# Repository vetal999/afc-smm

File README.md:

afc-smm
=======

project for my master degree diploma

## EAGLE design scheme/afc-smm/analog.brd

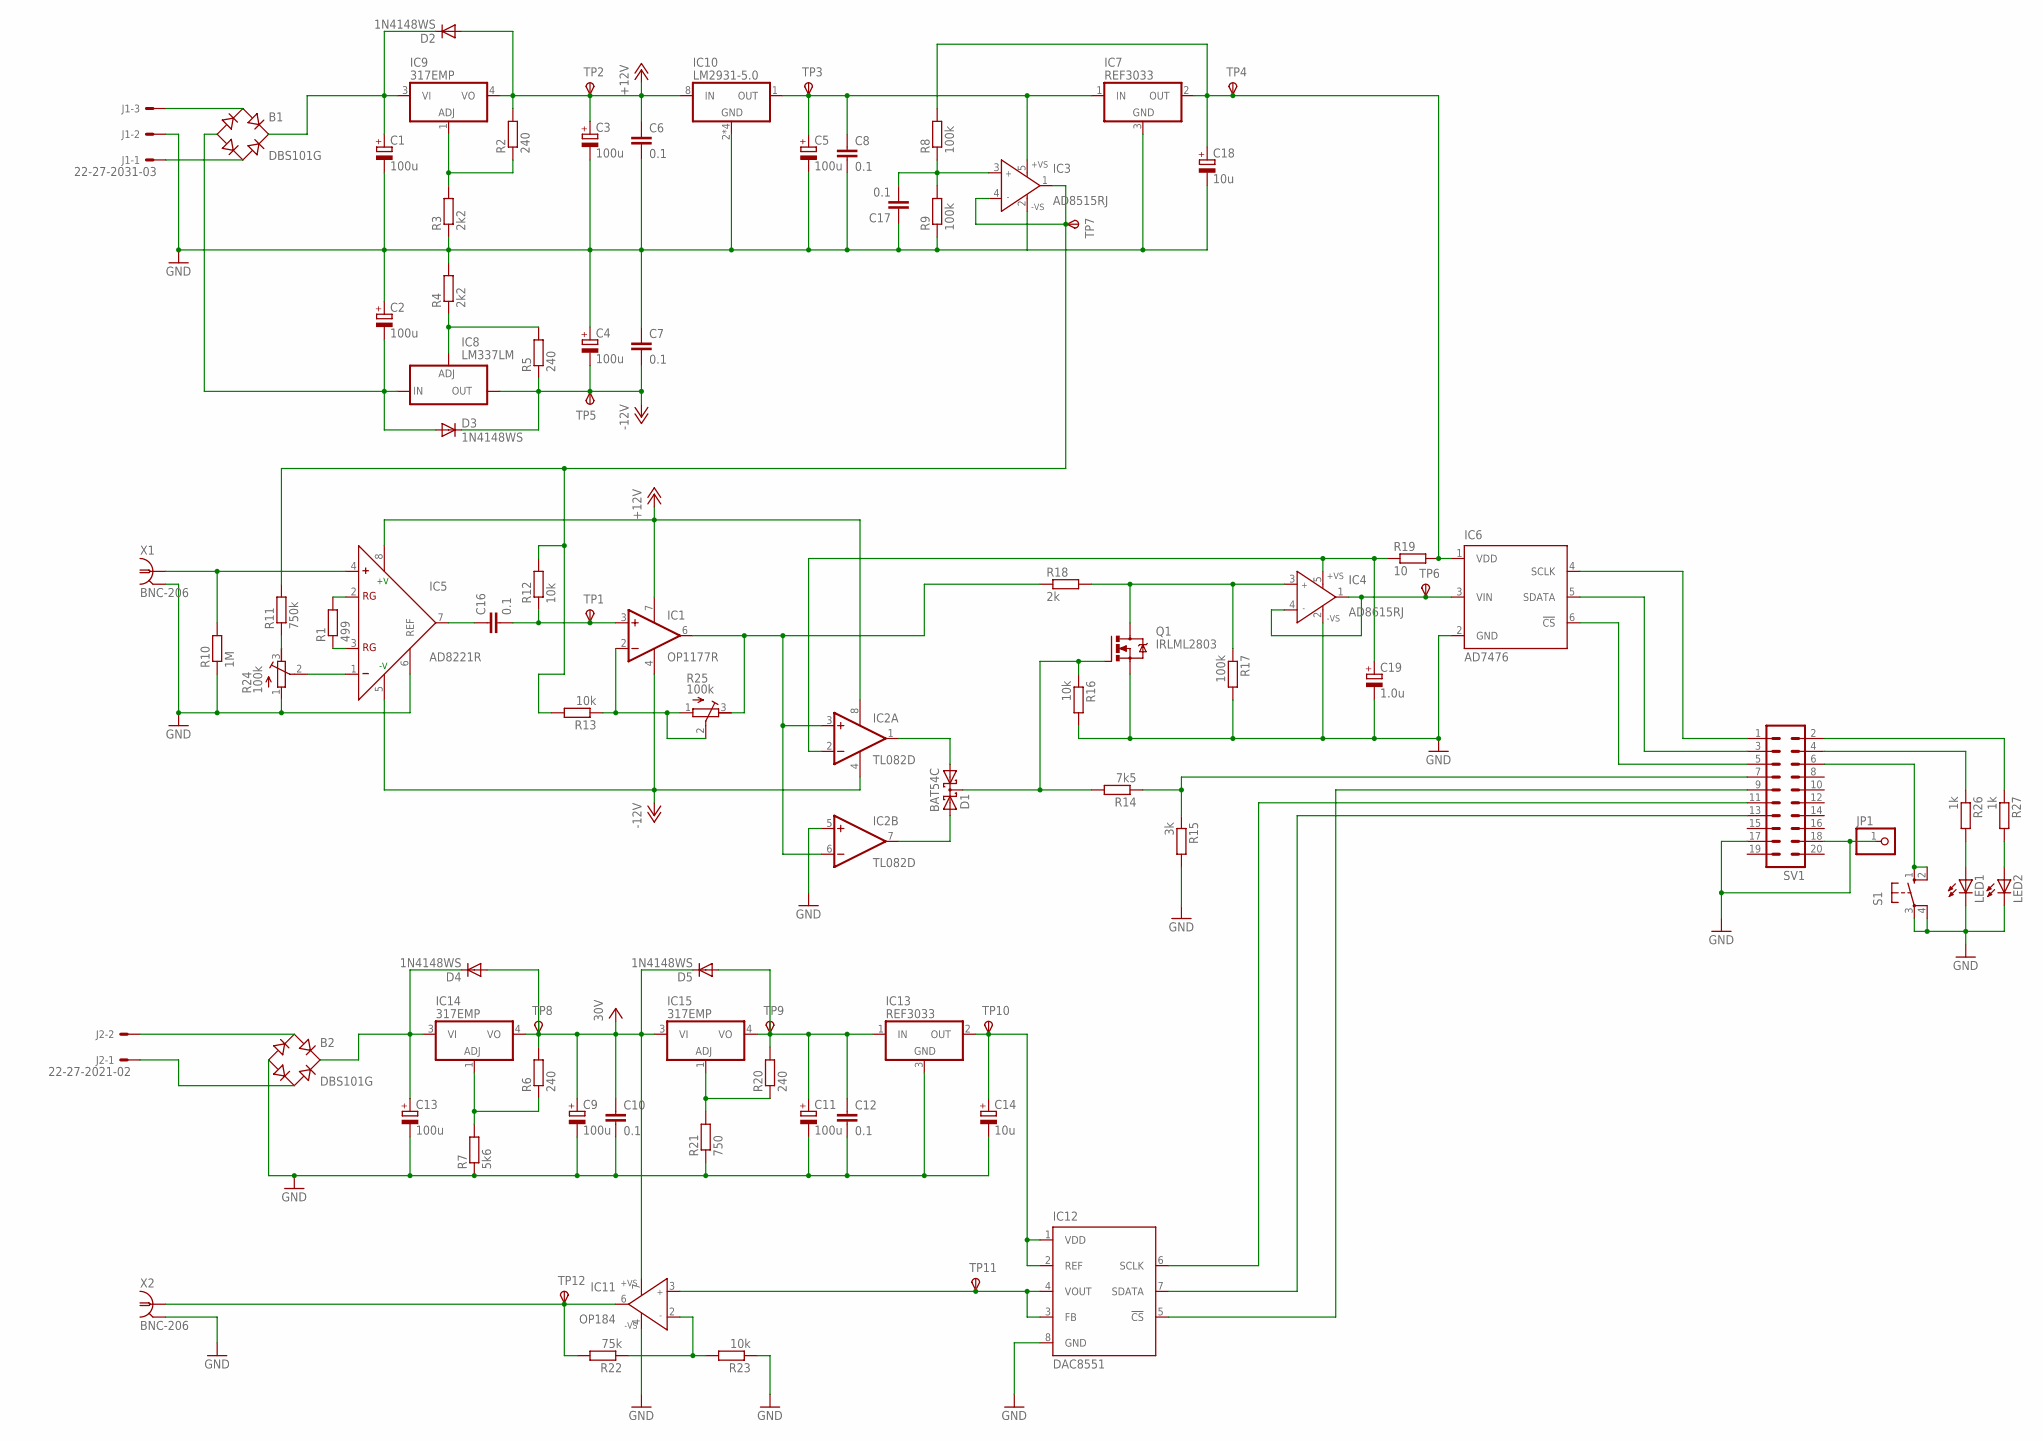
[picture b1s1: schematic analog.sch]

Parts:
B1, B2: DBS101G; DBS
C1, C2, C13: 100u; E3,5-8
C3, C4, C9: 100u; E2,5-6
C5, C11: 100u; E2,5-5
C6, C7, C10: 0.1; C0805K
C8, C12, C16, C17: 0.1; C0603
C14, C18: 10u; SMC_A
C19: 1.0u; SMC_A
D1: BAT54C; SOT23
D2, D3, D4, D5: 1N4148WS; SOD323
IC1: OP1177R; SOIC8
IC2: TL082D; SO08
IC3: AD8515RJ; SOT23-5
IC4: AD8615RJ; SOT23-5
IC5: AD8221R; SO8@1
IC6: AD7476; SOT23-6
IC7, IC13: REF3033; SOT23
IC8: LM337LM; SO8
IC9, IC14, IC15: 317EMP; SOT223
IC10: LM2931-5.0; SO8
IC11: OP184; SO8
IC12: DAC8551; MSOP8
J1: 22-27-2031-03; 6410-03
J2: 22-27-2021-02; 6410-02
JP1: PINHD-1X1; 1X01
LED1, LED2: LEDCHIPLED_0805; CHIPLED_0805
Q1: IRLML2803; SOT23
R1: 499; R0805
R2, R5, R6: 240; R0805
R3, R4: 2k2; R0805
R7: 5k6; R0805
R8, R9, R17: 100k; R0603
R10: 1M; R0603
R11: 750k; R0603
R12, R13, R16, R23: 10k; R0603
R14: 7k5; R0603
R15: 3k; R0603
R18: 2k; R0603
R19: 10; R0603
R20: 240; R0603
R21: 750; R0603
R22: 75k; R0603
R24, R25: 100k; RTRIM3296W
R26, R27: 1k; R0603
S1: 10-XX; B3F-10XX
SV1: MA10-2W
TP1, TP2, TP3, TP4, TP5, TP6, TP7, TP8, TP9, TP10, TP11, TP12: TPSB2,54; B2,54
X1, X2: BNC-206; AMP_227161

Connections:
30V: C9.+, C10.1, D4.2 (A), D5.1 (C), IC11.7 (+VS), IC14.4 (VO), IC15.3 (VI), R6.2, TP8.TP
+3.3V: C18.+, IC6.1 (VDD), IC7.2 (OUT), R8.2, R19.2, TP4.TP
+5V: C5.+, C8.1, IC3.5 (+VS), IC7.1 (IN), IC10.1 (OUT), TP3.TP
+12V: C3.+, C6.1, D2.2 (A), IC1.7 (V+), IC2.8 (V+), IC5.8 (+V), IC9.4 (VO), IC10.8 (IN), R2.2, TP2.TP
-12V: C4.-, C7.2, D3.1 (C), IC1.4 (V-), IC2.4 (V-), IC5.5 (-V), IC8.1 (OUT), R5.1, TP5.TP
GND: B2.-, C1.-, C2.+, C3.-, C4.+, C5.-, C6.2, C7.1, C8.2, C9.-, C10.2, C11.-, C12.2, C13.-, C14.-, C17.1, C18.-, C19.-, IC2.5 (+IN), IC3.2 (-VS), IC4.2 (-VS), IC5.6 (REF), IC6.2 (GND), IC7.3 (GND), IC10.2 (GND), IC10.3 (GND), IC10.6 (GND), IC10.7 (GND), IC11.4 (-VS), IC12.8 (GND), IC13.3 (GND), J1.2, JP1.1, LED1.C, LED2.C, Q1.2 (S), R3.1, R4.2, R7.1, R9.1, R10.1, R15.2, R16.2, R17.2, R21.1, R23.1, R24.1 (A), S1.3, S1.4 (P1), SV1.17, SV1.18, X1.2, X2.2
unnamed: IC4.1 (OUT), IC4.4 (IN-), IC6.3 (VIN), TP6.TP
unnamed: IC4.3 (IN+), Q1.3 (D), R17.1, R18.2
unnamed: B1.-, C2.-, D3.2 (A), IC8.2 (IN), IC8.3 (IN), IC8.6 (IN), IC8.7 (IN)
unnamed: D1.1 (A1), IC2.1 (OUT)
unnamed: D1.3 (CC), Q1.1 (G), R14.2, R16.1
unnamed: D1.2 (A2), IC2.7 (OUT)
unnamed: R26.1, SV1.4
unnamed: R14.1, R15.1, SV1.7
unnamed: IC1.6 (OUT), IC2.3 (+IN), IC2.6 (-IN), R18.1, R25.3 (E)
unnamed: IC5.2 (RG), R1.2
unnamed: IC5.3 (RG), R1.1
unnamed: C16.1, IC5.7 (OUT)
unnamed: IC1.2 (-IN), R13.1, R25.1 (A), R25.2 (S)
unnamed: IC6.4 (SCLK), SV1.1
unnamed: C16.2, IC1.3 (+IN), R12.1, TP1.TP
unnamed: LED1.A, R26.2
unnamed: IC5.1 (-), R24.2 (S)
unnamed: R11.1, R24.3 (E)
unnamed: IC5.4 (+), R10.2, X1.1
unnamed: LED2.A, R27.2
unnamed: IC6.5 (SDATA), SV1.3
unnamed: IC6.6 (!CS), SV1.5
unnamed: B2.AC1, J2.2
unnamed: IC8.4 (ADJ), R4.1, R5.2
unnamed: IC9.1 (ADJ), R2.1, R3.2
unnamed: R27.1, SV1.2
unnamed: C19.+, IC2.2 (-IN), IC4.5 (+VS), R19.1
unnamed: IC3.1 (OUT), IC3.4 (IN-), R11.2, R12.2, R13.2, TP7.TP
unnamed: C17.2, IC3.3 (IN+), R8.1, R9.2
unnamed: B2.+, C13.+, D4.1 (C), IC14.3 (VI)
unnamed: C11.+, C12.1, D5.2 (A), IC13.1 (IN), IC15.4 (VO), R20.2, TP9.TP
unnamed: IC14.1 (ADJ), R6.1, R7.2
unnamed: B1.AC1, J1.3
unnamed: B1.AC2, J1.1
unnamed: IC15.1 (ADJ), R20.1, R21.2
unnamed: B1.+, C1.+, D2.1 (C), IC9.3 (VI)
unnamed: C14.+, IC12.1 (VDD), IC12.2 (REF), IC13.2 (OUT), TP10.TP
unnamed: IC12.6 (SCLK), SV1.11
unnamed: IC11.6 (OUT), R22.2, TP12.TP, X2.1
unnamed: IC12.7 (SDATA), SV1.13
unnamed: IC11.2 (IN-), R22.1, R23.2
unnamed: IC12.5 (!CS), SV1.9
unnamed: IC11.3 (IN+), IC12.3 (FB), IC12.4 (VOUT), TP11.TP
unnamed: B2.AC2, J2.1
unnamed: S1.1 (S), S1.2 (S1), SV1.6

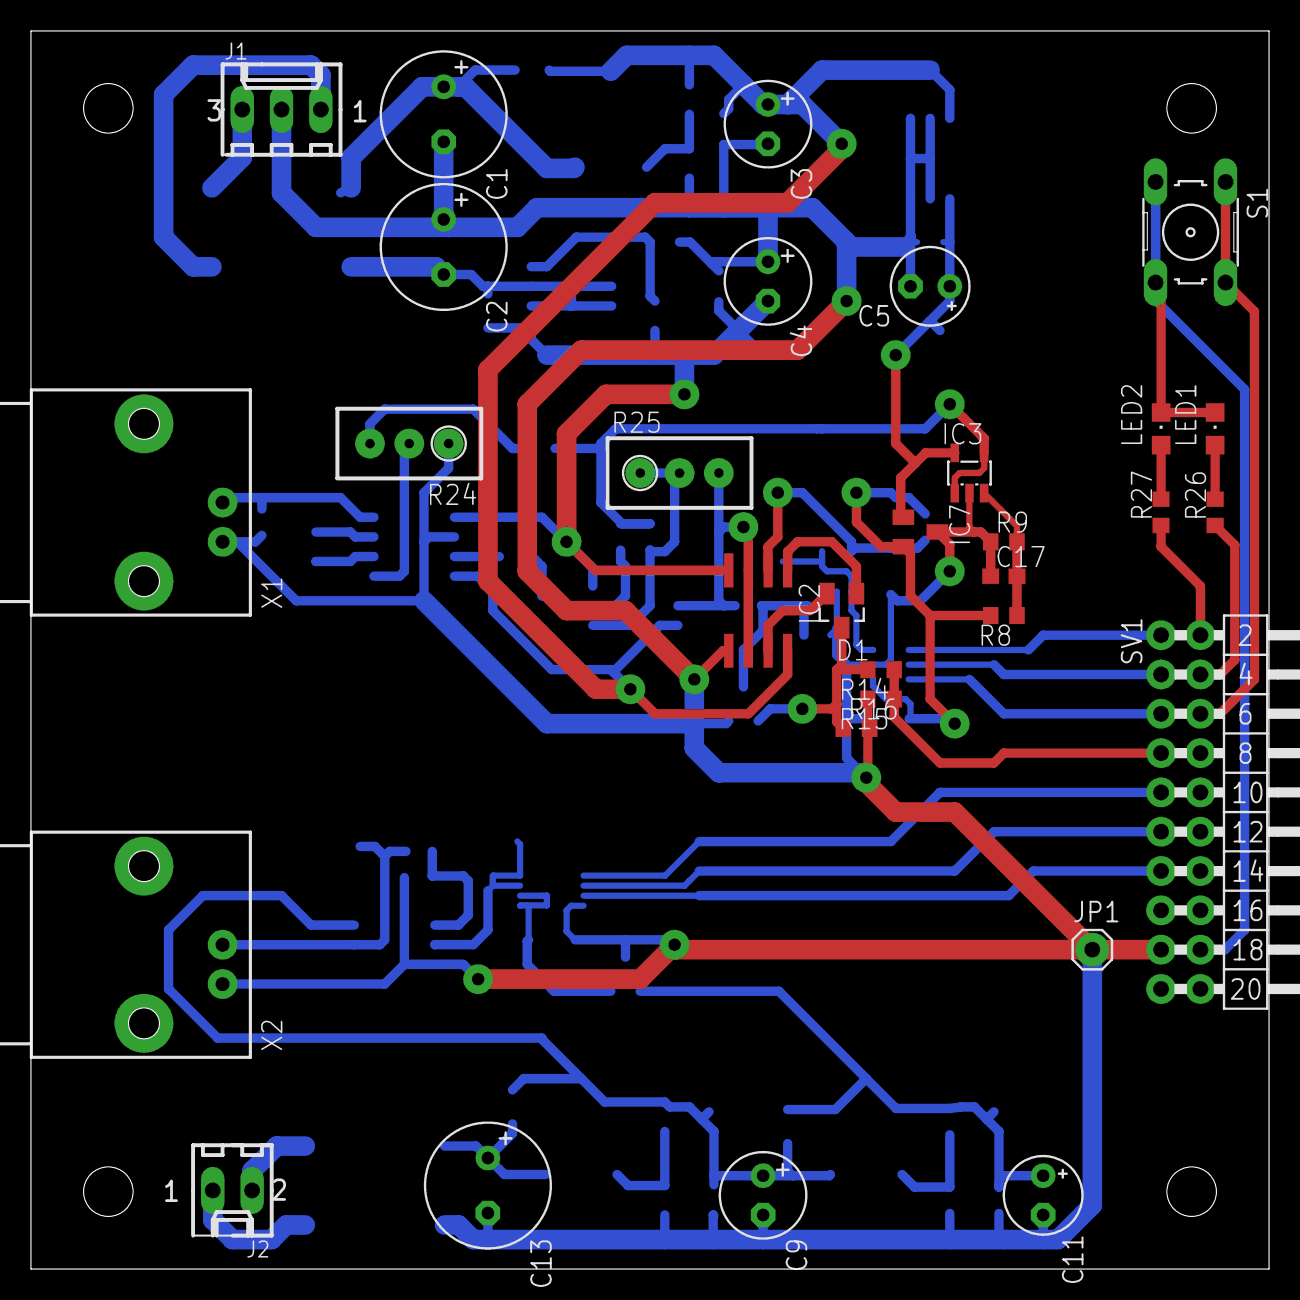
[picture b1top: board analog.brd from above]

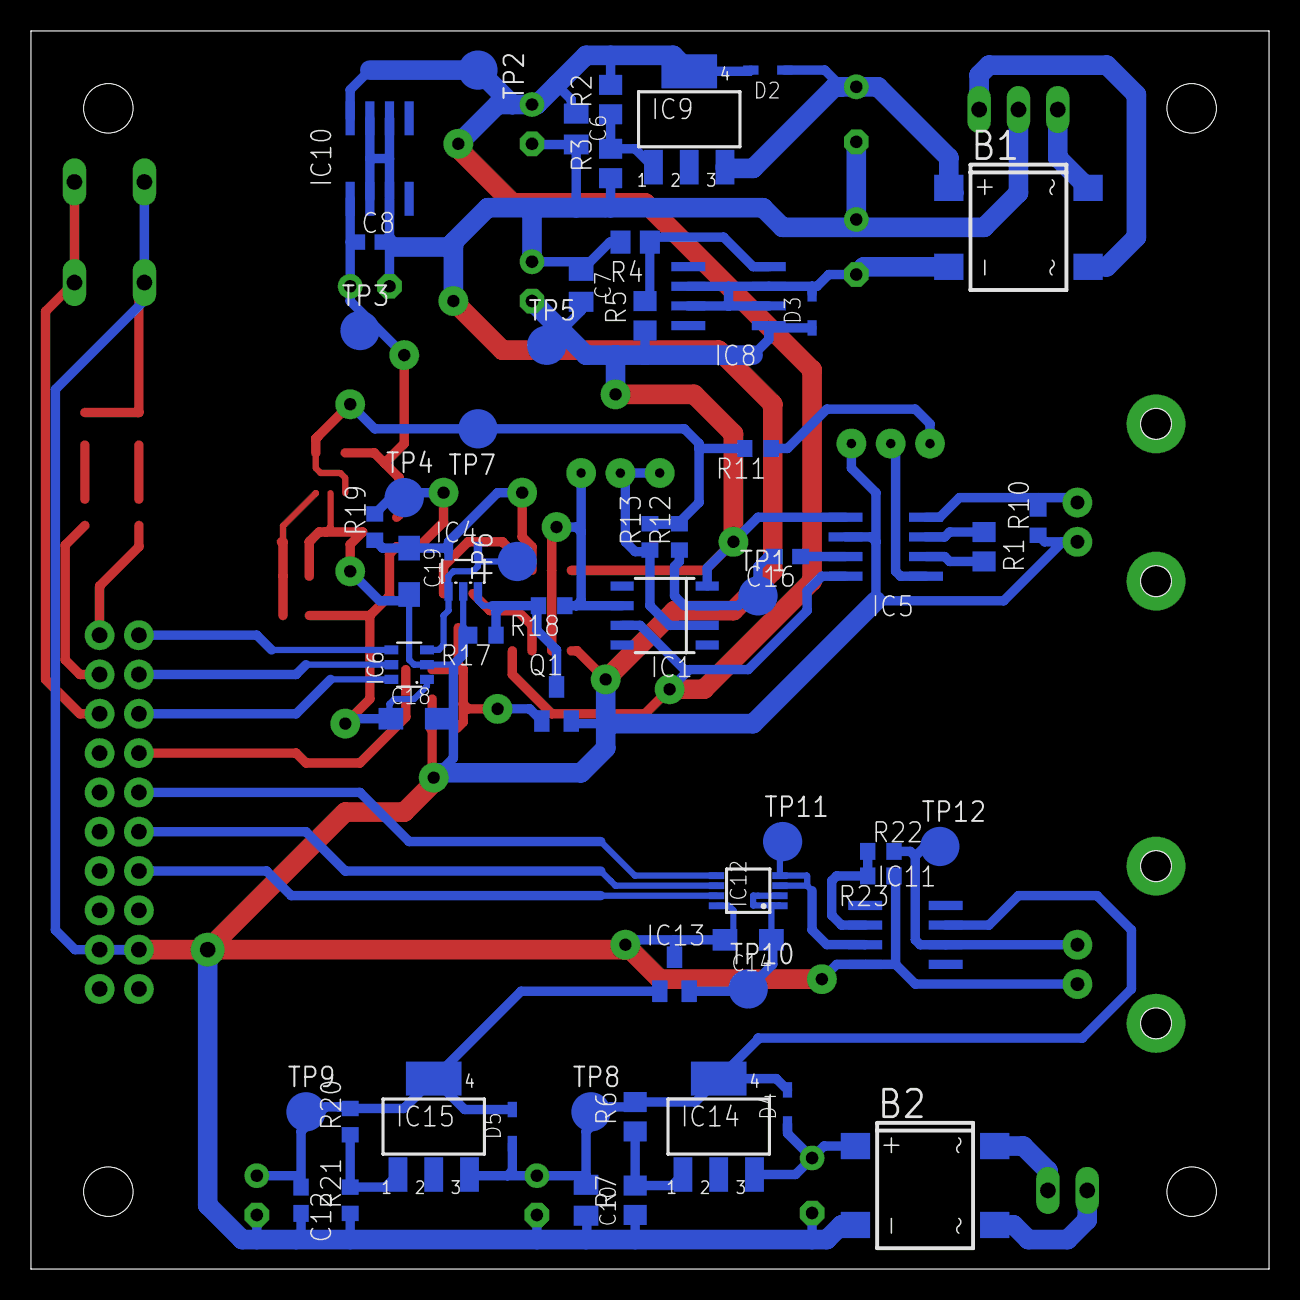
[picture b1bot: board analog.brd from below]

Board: 2 copper layers, 80.0 x 80.0 mm, 89 parts (58 on the bottom side), 51 nets.

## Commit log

2014-02-05 create some components and start to draw schematic
2014-02-07 add some element on schematic, begin connecting
2014-02-10 start to make raw PCB
2014-02-11 commit before vocation
2014-02-18 make analog in, not compleate yet
2014-02-21 make analog out schematics, draw most of brd
2014-02-24 compleat? version 0.1 first
2014-03-06 little improvement after production
2014-03-06 add component value
2014-03-10 some bugfix after assembly, not all bugfix yet (capacitor for example and ground in dac)
2014-03-10 set pad at the BNC connector bigger
2014-04-03 create qurtus project, add led blinking
2014-04-05 add PLL, ADC works, clock 20 MHz, 1 MSPS
2014-04-05 add DAC, works good
2014-04-05 add debug interface with uart2bus
2014-04-11 add dds_synthesizer, try to use FFT256, create script for uart2bus
2014-04-19 check DAC on real generator, trouble with FFT and aplitude of inpute signal, need to reduce modulation depth
2014-05-02 create own spi_adc
2014-05-04 FFT works!
2014-05-20 it is work! go to add pid_controller
2015-05-17 Imported from https://vetal999@github.com/vetal999/afc-smm.git
